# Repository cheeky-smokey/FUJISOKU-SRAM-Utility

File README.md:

# FUJISOKU SRAM Utility

> **このブランチ（`wo62256`）は v3.0 です。まだ実機では確かめていません。**
> 62256 をやめ、カードの F32〜F35（A16〜A19）を MCP23S17 ch7（U2）の GPB4〜GPB7 につなぐ設計にしました。カードは PC から 1MB まで読み書きできます。v2.8 の基板とは ch7 ポート B の配線が違います（[v2.8 からの変更](#v28-からの変更ハードウェア)）。
> 動作確認済みのリリース版 v2.8 は main ブランチと [Releases](https://github.com/cheeky-smokey/FUJISOKU-SRAM-Utility/releases) にあります。

Silver Reed 編み機のメモリカード（FUJISOKU SRAM、基本は 32KB。PC からは 1MB まで）を、Arduino UNO R4 で読み書きするツールです。MCP23S17 を 2 個使った GPIO エキスパンダでカードのアドレス・データ・制御線を直接動かし、PC・SD カード・SPI SRAM との間でコピーと照合をします。

- **PC から操作**: ブラウザの Web アプリで、カードを PC に保存・PC のファイルをカードに書き込み・比較。読み込みも書き込みも 32KB〜1MB の大きさをボタンで選べます。
- **表示**: 状態・処理の段階・進捗バー・結果を 20 文字 × 4 行で表示。同じ画面が Web アプリにも出るので、LCD はオプションです。
- **SD カード（オプション）**: 本体だけでカード ⇄ SD のバックアップ・照合・書き戻し。SD カードは処理の合間に抜き差しでき、最初から入っていなくても止まりません。
- **カードの検出と電池電圧**: カードが入っていなければ操作を止め、カードの電池電圧を LCD と Web アプリに表示します。1.70 V 以下で「少ない」（Low battery）、0.50 V 以下で「電池なし」と警告します。
- **シールド基板とスロットユニット**: Arduino UNO R4 に重ねるシールド基板（KiCad、ガーバー付き）に、U-BOX から外したスロットで作るスロットユニットを直接挿します。

## 使い方

1. 本体にこのブランチのスケッチ（v3.0）を書き込み、USB で PC につなぐ。
2. PC の **Google Chrome** または **Microsoft Edge** で [`webapp/FSRAM-Utility.html`](webapp/FSRAM-Utility.html) を開き、「本体に接続」を押してシリアルポートを選ぶ。
3. 目的のタブを選ぶ。

| タブ | できること |
|---|---|
| PC に保存 | カードを読み込んで `.bin` に保存。読み込む大きさは 32KB（既定）/ 64KB / 128KB / 256KB / 512KB / 1MB のボタンで選ぶ。2 回読んで一致を確かめる設定あり |
| カードに書き込み | `.bin`（32KB〜1MB）をカードへ。書き込む大きさは 32KB / 64KB / 128KB / 256KB / 512KB / 1MB のボタンで選ぶ（既定はファイルの大きさ）。32KB より大きく書くときは「先頭 32KB だけ」か「すべて」かを警告で選ぶ。書き込む前の自動保存、変わった部分だけの書き込み、書き込み後の照合 |
| 比較 | カードとファイル、またはファイル同士を比較。違いはメモリマップと 16 進表示に赤で出る |
| SD カード | 本体の SD カードとの保存・照合・書き込み、ファイル一覧（SD を使う設定のときだけ表示） |
| SPI SRAM・診断 | SPI SRAM とのコピー・比較・消去、SPI SRAM の自己診断（SPI SRAM を使う設定のとき）、カードの消去 |

「カードに書き込み」「比較」のファイル欄は、クリックかドロップで選び直せ、右の × で外せます。ふつうのカードは 32KB です。容量の大きいカードのときだけ大きさを変えてください（32KB のカードに 32KB を超えて書くと、先頭が上書きされます）。

Web アプリの詳しい説明は [docs/webapp.md](docs/webapp.md)、シリアルコマンドは [docs/protocol.md](docs/protocol.md) にあります。従来の 1 文字コマンド（`B` `L` `V` `R` `C` `X` `S` `W` `T` `E` `e`）もそのまま使えます。

## ハードウェア

### 必要なもの

| 区分 | 部品 | `config.h` |
|---|---|---|
| 必須 | Arduino UNO R4（Minima / WiFi） | - |
| 必須 | [シールド基板](#シールド基板) rev 2.0（MCP23S17 × 2 などを載せる。ユニバーサル基板で同じ結線にしてもよい） | - |
| 必須 | [スロットユニット](#スロットユニット)（U-BOX から外したスロット + 変換基板 + L 型のキー付きボックスヘッダ） | - |
| オプション | 20 × 4 キャラクタ LCD（HD44780 + PCF8574 の I2C バックパック。5V・GND・SDA = A4・SCL = A5） | `USE_LCD`（既定 1） |
| オプション | SD カードモジュール（5 V で使えるもの。/CS は D7） | `USE_SD`（既定 0） |
| オプション | SPI SRAM（23LC512。本体だけでのコピー・比較の一時置き場。/CS は D6） | `USE_SPI_SRAM`（既定 1。起動時に自動検出） |
| 配線 | カードの検出（カードの F37 /CARD DET → D2。シールド基板は配線済み） | `USE_CARD_DET`（既定 1） |
| 配線 | 電池電圧（カードの F2 BATT-DET → A2。A2 と GND の間に 1 MΩ。シールド基板は配線済み） | `USE_BATT_DET`（既定 1） |

カードの吸い出し・書き込み・比較は Web アプリでできるので、必須なのは Arduino UNO R4、シールド基板（MCP23S17 × 2）、スロットユニットだけです。電源は 5 V で、部品はすべて 5 V 系なのでレベル変換は要りません。

### シールド基板

| 項目 | 内容 |
|---|---|
| 大きさ | 68.58 × 53.34 mm（Arduino UNO と同じ形。右側の角が斜め） |
| 層・厚さ | 2 層、1.6 mm |
| 部品 | すべてスルーホール、IC は DIP（MCP23S17 × 2、23LC512、カードの電源のコンデンサ、BATT-DET のプルダウン、SD・LCD 用のピンヘッダ） |
| 取り付け穴 | φ3.2 mm × 4（UNO と同じ位置） |
| カードの接続 | J1 = キー付き MIL メスソケット 40P（キーは奥 = U1 側）。スロットユニットを直接挿す |
| データ | [hardware/kicad/shield/](hardware/kicad/shield/)（`.kicad_pcb`、ガーバー zip、原寸 PDF） |

部品表・注文のしかた（JLCPCB などの設定）・組み立ての注意は [hardware/kicad/README.md](hardware/kicad/README.md#シールド基板arduino-uno-r4-用) にあります。

### スロットユニット

FUJISOKU のカードスロットは製造中止なので、U-BOX から外したスロットを使います。スロットの足（ZIP 配列）を、秋月電子の 2.54 mm（2×5）⇔ 1.27 mm（1×10）変換基板 4 枚（表裏を逆にして使う）で 2 列にし、L 型のキー付きボックスヘッダ（2×20）を付けます。

- **シールドにつなぐ**: シールドの J1 に直接挿します。ボックスヘッダの切り欠きにソケットのキーが入るので、逆向きには挿さりません。
- **U-BOX につなぐ**: U-BOX の CN2 に足を ZIP 配列に曲げたボックスヘッダを付け、ストレートの 40 芯リボンケーブルでつなぎます。
- **ヘッダのピン**: 1 番 = F2、2 番 = F1（下段）、3 番 = F4、4 番 = F3 … 37 番 = F38、38 番 = F37。39・40 番は空き（奇数ピン 2k−1 = F2k、偶数ピン 2k = F2k−1）。

作り方と参考写真は [docs/hardware.md §12](docs/hardware.md#12-スロット記事より) にあります。

### カードの信号の割り当て（v3.0）

| 信号 | カードのピン | つなぐ先 |
|---|---|---|
| A0〜A15 | F16〜F31 | ch6（U1）の GPA0〜GPA7・GPB0〜GPB7 |
| D0〜D7 | F8〜F15 | ch7（U2）の GPA0〜GPA7 |
| CE2 / /OE / /CE1 / /WE | F5 / F7 / F4 / F6 | ch7（U2）の GPB0 / GPB1 / GPB2 / GPB3 |
| A16〜A19 | F32〜F35 | ch7（U2）の GPB4〜GPB7 |
| BATT-DET / /CARD DET | F2 / F37 | Arduino の A2 / D2 |
| Vcc / GND | F3・F36 / F1・F38 | 5 V / GND |

詳しい結線表・ピン配置・アクセス手順は [docs/hardware.md](docs/hardware.md) にあります。KiCad の回路図（PDF 付き）は [hardware/kicad/](hardware/kicad/) にあります。

### v2.8 からの変更（ハードウェア）

| 項目 | v2.8（main） | v3.0（このブランチ） |
|---|---|---|
| ch7 GPB0〜GPB3 | CE2（62256 の /CS と共用）、/OE、62256 の /OE、/WE | CE2、/OE、**/CE1**、/WE |
| ch7 GPB4〜GPB7 | /CE1、未使用、A16、A17 | **A16、A17、A18、A19** |
| カードの F34・F35（A18・A19） | GND に固定 | **U2 の GPB6・GPB7** |
| カードの範囲（PC から） | 256KB（A0〜A17） | **1MB（A0〜A19）** |
| 62256 | オプション（`USE_SRAM62256`） | **使わない** |
| シールド基板 | rev 1.x | **rev 2.0**（U2 の GPB の配線が違う。ガーバーも別） |

v2.8 の基板を v3.0 で使うときは、ch7 の GPB2 と GPB4〜GPB7 の配線を上の表のとおりにやり直してください。

## 設定（`config.h`）

オプション部品は `FUJISOKU_SRAM_COPY/config.h` の先頭で選びます。既定は SD カードなし、LCD と SPI SRAM はあり（どちらも見つからなければ飛ばして動く）です。

```c
#define USE_SD 0          // SD カードをつないだら 1 (SdFat ライブラリが要る)
#define USE_LCD 1         // LCD をつながないなら 0 (LiquidCrystal I2C ライブラリも不要になる)
#define USE_SPI_SRAM 1    // SPI SRAM をつながないなら 0 (1 のままでも、見つからなければ飛ばす)
#define USE_CARD_DET 1    // D2 にカードの検出を配線していないなら 0
#define USE_BATT_DET 1    // A2 にカードの電池電圧を配線していないなら 0
#define BATT_NONE_MV 500  // これ以下は「電池なし」(No battery) [mV]
#define BATT_LOW_MV 1700  // これ以下は「少ない」(Low battery) [mV]。BATT_NONE_MV より大きくする
```

`USE_LCD` と `USE_SPI_SRAM` は 1 のままでも、起動時に見つからなければその部品を使わずに動きます（SPI SRAM を使う操作は `ERR NOSPI` になり、Web アプリは自己診断だけを出します）。LCD の I2C アドレスは `LCD_I2C_ADDR`（既定 `0x27`、表示されないときは `0x3F`）です。

## ビルド

1. Arduino IDE のライブラリマネージャで、使う部品に合わせて入れる（SD と LCD を使わないなら不要）。
   - **SdFat**（Bill Greiman、v2 系）。`USE_SD` を 1 にしたときだけ必要です（既定の 0 なら不要）。
   - **LiquidCrystal I2C**（Frank de Brabander）。`USE_LCD` が 1 のときだけ必要です。「AVR 用」と警告が出ることがありますが、UNO R4 でも使えます。
2. `FUJISOKU_SRAM_COPY/FUJISOKU_SRAM_COPY.ino` を開いてボードに書き込む（同じフォルダの `.ino` と `config.h` はタブとして一緒に開かれます）。

## 構成

```
FUJISOKU_SRAM_COPY/         スケッチ (メイン、config.h、hardware / storage / operations / protocol / lcd_ui / card)
webapp/FSRAM-Utility.html   Web アプリ (1 ファイル、インストール不要)
docs/                       hardware.md (配線)、specification.md (ソフト仕様)、protocol.md (通信)、webapp.md
hardware/kicad/             KiCad の回路図 (.kicad_sch、PDF)、作り直し・確認用のスクリプト
hardware/kicad/shield/      UNO R4 用シールド基板 rev 2.0 (.kicad_pcb、ガーバー zip、原寸 PDF)
test/                       PC 上でスケッチを動かすシミュレータと自動テスト (test/README.md)
```

## 確かめたこと

スケッチをそのまま PC でビルドし、MCP23S17・カード・SPI SRAM・SD カード・LCD を再現したシミュレータで動かして、66 件の自動テスト（ファームウェア 30、表示 9、Web アプリ 27。SD・LCD・SPI SRAM・カード検出のあり・なしの構成と、1MB のカードの読み書きを含む）が通ることを確認しています。本物の SdFat と LiquidCrystal I2C のヘッダに対する型チェックも通っています。シールド基板は DRC（エラー 0、未配線 0）と、銅のつながりを [docs/hardware.md](docs/hardware.md) の結線表と照らし合わせて確かめています。変更点は [docs/specification.md §12](docs/specification.md#12-変更履歴)、テストは [test/README.md](test/README.md) にあります。

**実機（Arduino UNO R4 と作者の基板）での動作は v2.8 まで確認済みです。v3.0 の新しい割り当てとシールド基板 rev 2.0 は、まだ実機で確かめていません。**

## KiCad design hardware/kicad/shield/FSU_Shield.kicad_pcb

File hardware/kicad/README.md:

# 回路図・シールド基板（KiCad）

FUJISOKU SRAM Utility の回路図と、Arduino UNO R4 用のシールド基板です。[docs/hardware.md](../../docs/hardware.md) の結線表と `FUJISOKU_SRAM_COPY/config.h` のピン定義（v3.0、ブランチ `wo62256`）から作りました。シールド基板は rev 2.0 で、main（v2.8）の rev 1.x とは U2 GPB の配線が違います。**v3.0 の割り当ては、まだ実機では確かめていません。**

- [回路図](#回路図)（スロットも含む全体）
- [シールド基板](#シールド基板arduino-uno-r4-用)（ガーバー付き。カードのスロットユニットを J1 に直接挿す）
- [スロットユニット](#スロットユニット)（U-BOX から外したスロット + 変換基板 + L 型ボックスヘッダ）

## 回路図

| ファイル | 内容 |
|---|---|
| `FUJISOKU_SRAM_Utility.kicad_pro` / `.kicad_sch` | KiCad のプロジェクトと回路図（KiCad 7 で作成。8 / 9 でも開ける） |
| `FUJISOKU_SRAM_Utility.pdf` | 印刷・閲覧用の PDF（A3） |
| `gen_schematic.py` | 回路図を作るスクリプト。結線を変えるときはここを直して作り直す（`--shield` でシールド基板用の回路図） |
| `check_netlist.py` | 回路図の結線が仕様書どおりかを確かめるスクリプト（`--shield` でシールド基板用） |

### 載っている部品

| 部品番号 | 部品 | 備考 |
|---|---|---|
| A1 | Arduino UNO R4 | KiCad の UNO R3 の形（ピン配置は同じ） |
| U1 | MCP23S17 ch6 | アドレス A0〜A15。A2:A0 = 110 |
| U2 | MCP23S17 ch7 | データ D0〜D7、制御線（GPB0〜GPB3）、A16〜A19（GPB4〜GPB7）。A2:A0 = 111 |
| J1 | FUJISOKU カードのスロット（F1〜F38） | ピン番号 n = カードのピン Fn。F32〜F35 = A16〜A19（U2 GPB4〜GPB7） |
| R1 | 1 MΩ | BATT-DET（A2）のプルダウン |
| U3 | 23LC512（オプション） | SPI SRAM、/CS = D6 |
| J2 | SD カードモジュール（オプション） | 5 V 用。/CS = D7。ピンの並びはモジュールによって違う |
| J3 | 20×4 LCD + PCF8574（オプション） | I2C、アドレス 0x27 |
| C1〜C3 / C4 | 0.1 µF / 10 µF | 各 IC の近くのパスコンと電源の電解コンデンサ（推奨。仕様書には無い部品） |

- 部品どうしは、ピンに付けた名前（ネットラベル）でつないでいます。同じ名前のラベルがつながっています。
- 電源は Arduino の 5V ピンから取る 5 V だけです。部品はすべて 5 V 系で、レベル変換はありません。

## シールド基板（Arduino UNO R4 用）

| 表 | 裏（裏から見た向き） |
|---|---|
|  |  |

- 大きさは Arduino UNO と同じ（68.58 × 53.34 mm、右側の角が斜め）。2 層、厚さ 1.6 mm。取り付け穴は φ3.2 mm × 4（UNO と同じ位置）。UNO R4 Minima / WiFi に重ねて使います。
- 部品はすべてスルーホールで、IC は DIP（ソケット）です。
- カードは、[スロットユニット](#スロットユニット)を **J1（キー付きの MIL メスソケット）に直接挿して**つなぎます。ユニットのボックスヘッダの切り欠きにソケットのキーが入るので、逆向きには挿さりません。キーは奥（U1 側、シルクの KEY）です。
  J1 のピンとカードのピンの対応は、スロットユニットのヘッダと同じです。

  | J1 のピン | 1 | 2 | 3 | 4 | 5 | 6 | … | 37 | 38 | 39 | 40 |
  |---|---|---|---|---|---|---|---|---|---|---|---|
  | カード | F2 | F1 | F4 | F3 | F6 | F5 | … | F38 | F37 | 空き | 空き |

  （2k−1 番 = F2k、2k 番 = F2k−1）。F32〜F35（A16〜A19）は U2 の GPB4〜GPB7 につないでいます。
- 配線は自動配線（Freerouting）で、表と裏に GND のベタを敷いています。ビアは 13 個です。
- 確認済み: DRC（設計ルールの確認）でエラーと未配線は 0、基板の銅のつながりを `check_netlist.py --shield` で仕様書の結線表と照合。

### ファイル（`shield/`）

| ファイル | 内容 |
|---|---|
| `gerber/FSU_Shield_gerber.zip` | **基板メーカーに出すデータ**（ガーバーとドリル） |
| `FSU_Shield.kicad_pro` / `.kicad_pcb` / `.kicad_sch` | KiCad のプロジェクト、基板、回路図 |
| `FSU.pretty/`、`fp-lib-table` | シールド用の Arduino のフットプリント（下の注意を参照）と、J1 のキー付きメスソケットのフットプリント |
| `FSU_Shield_top.png` / `_bottom.png` | 基板の見た目（確認用） |
| `FSU_Shield_1to1.pdf` | 原寸の図（A4 に 100 % で印刷して Arduino を重ね、ピンの位置を確かめる用） |
| `drc_report.txt` | DRC の結果 |
| `../gen_pcb.py` | 基板を作るスクリプト（配置、自動配線、ベタ、DRC、ガーバー） |

### 部品表

| 部品番号 | 部品 | 個数 | 備考 |
|---|---|---|---|
| U1, U2 | MCP23S17-E/SP（DIP-28、幅 7.62 mm） | 2 | 28 ピン IC ソケット（300 mil）を使う |
| U3 | 23LC512-I/P（DIP-8） | 1 | オプション。8 ピン IC ソケット。挿さなくても動く（自動検出） |
| J1 | MIL コネクタのメスソケット 40P（2×20、2.54 mm、基板用ストレート、キー付き） | 1 | ボックスヘッダに挿さるもの。キーを奥（U1 側、シルクの KEY）に向ける |
| J2 | ピンヘッダ 1×6 | 1 | SD カードモジュール（オプション）。ジャンパ線でつなぐ |
| J3 | ピンヘッダ 1×4 | 1 | LCD（オプション）。GND、5V、SDA、SCL |
| R1 | 1 MΩ 1/4 W | 1 | BATT-DET（A2）のプルダウン |
| C1〜C3 | 0.1 µF 積層セラミック、足の間隔 5 mm（5.08 mm の部品も入る） | 3 | U1〜U3 のパスコン。VDD・VSS のピンのすぐ横 |
| C4 | 10 µF 電解（16 V 以上、直径 5 mm、足の間隔 2.5 mm。2 mm の部品は足を少し広げて挿す） | 1 | カードの電源用。+ の向きに注意 |
| — | ピンヘッダ（オス）1×10、1×8、1×8、1×6 | 各 1 | Arduino に挿す側。普通のシールドと同じく裏から差して表ではんだ付け |

### 注文のしかた

1. `shield/gerber/FSU_Shield_gerber.zip` を、そのまま JLCPCB、PCBWay、Elecrow などにアップロードします。
2. 設定は標準のままで作れます: 2 層、1.6 mm、線幅 0.3 mm 以上（電源 0.6 mm）、間隔 0.25 mm 以上、ビア 0.8 mm（穴 0.4 mm）。層数と大きさはガーバーから自動で読み取られます。JLCPCB の場合の例:

   | 項目 | 設定 |
   |---|---|
   | Base Material / Layers | FR-4 / 2 |
   | PCB Qty | 5（最少） |
   | Delivery Format | Single PCB |
   | PCB Thickness | 1.6 mm |
   | PCB Color / Silkscreen | Green / White（ほかの色は高くなったり日数が延びたりすることがある） |
   | Surface Finish | HASL（有鉛または鉛フリー。スルーホールだけなので ENIG は要らない） |
   | Outer Copper Weight | 1 oz |
   | Mark on PCB（注文番号） | Remove Order Number（1〜6 層は手数料なし） |
   | そのほか | 既定のまま |
3. 注文の前に、`FSU_Shield_1to1.pdf` を A4 に **100 %（拡大縮小なし）** で印刷し、Arduino を重ねてピンの位置を確かめると確実です。

### 組み立て・使うときの注意

- **IC の向きに注意**: U1・U2 は U3 と逆向きです（U1・U2 は切り欠きが右、1 番ピンが右上。U3 は切り欠きが左、1 番ピンが左下）。シルクの切り欠きと四角いパッド（1 番ピン）に合わせて挿します。
- **J1 はキー（シルクの KEY と四角い出っ張り）を奥（U1 側）に向けて**付けます。1 番ピン（▽ の印、四角いパッド）は右端です。
- スロットユニットは、変換基板が手前（電源ヘッダ側）、カードのラベル面が奥を向く向きで挿さります。ボックスヘッダの口はシールドから約 2 mm 上に来るので、J1 の周りには背の高い部品を置いていません。
- **DC ジャック（左下）と ICSP ヘッダ（右の中ほど）の上には、部品の足が出ないように**配置してあります。USB-C の上（左上）には U3 があります（UNO R4 の USB-C は背が低いので当たりません）。
- 部品面の左下（取り付け穴の上、C4 の左）のシルクに「Powered by」「Cheeky-Smokey」の 2 行で入れています。
- MCP23S17 のアドレス（A2:A0）は基板の配線で決めてあります（U1 = 110、U2 = 111）。設定は要りません。
- J2（SD）は、モジュールによってピンの並びが違うので、シルクの名前（GND、5V、MISO、MOSI、SCK、CS）を見てジャンパ線でつなぎます。5 V で使えるモジュールを使います。
- U2 の GPB は B0 = CE2、B1 = /OE、B2 = /CE1、B3 = /WE、B4〜B7 = A16〜A19 です（v2.8 では /CE1 が B4、F34・F35 が GND）。

### スロットユニット

FUJISOKU のカードスロットは製造中止で手に入らないため、U-BOX から外したスロットを使い、シールドにも U-BOX にもつなげるユニットにします。

| 部品 | 個数 | 備考 |
|---|---|---|
| FUJISOKU カードスロット（U-BOX から外したもの） | 1 | 足は ZIP 配列。1 列にそろえて変換基板の 1.27 mm の穴に挿す |
| 秋月電子 2.54 mm（2×5）⇔ 1.27 mm（1×10）変換基板 | 4 | **表裏を通常と逆にして**使う。40 か所のうち 38 か所を使う |
| L 型（ライトアングル）ボックスヘッダ 2×20、2.54 mm、キー付き | 1 | 変換基板の 2×5 の穴に付ける |

- ヘッダの 1 番 = F2（上段）、2 番 = F1（下段 = 変換基板に近い列）… 37 番 = F38、38 番 = F37。39・40 番は空き。変換基板を表裏逆にするのは、奇数の F を下段にするためです。
- **シールドにつなぐ**: J1 に直接挿します（上の注意を参照）。
- **U-BOX につなぐ**: U-BOX の CN2 に、足を ZIP 配列に曲げたボックスヘッダを付け、ストレートの 40 芯リボンケーブル（両端 IDC ソケット）でつなぎます。CN2 の 1 番（F1）はボックスヘッダの 2 番に来るので、スロットユニットも 2 番 = F1 にしています。
- 切り欠き（キー）の位置は製品によって違うことがあります。買ったボックスヘッダとソケットで、正しい向きのときだけ挿さることを確かめてください。

### KiCad の標準の Arduino のフットプリントについて

KiCad 標準の `Module:Arduino_UNO_R3` は、上から見るとデジタル側のヘッダが下に来る向き（Arduino を裏返して載せる向き）で描かれています。シールドにそのまま使うと鏡に映した形になり、Arduino に挿せません。この基板では、それを上下反転した `FSU:Arduino_UNO_R4_Shield`（`shield/FSU.pretty`、原点は Arduino の基板の左下）を使っています。パッド番号は標準と同じなので、シンボル `MCU_Module:Arduino_UNO_R3` とそのまま対応します。

## 作り直す・確かめる

KiCad 7 以降が入った PC で次を実行します。

```sh
python3 gen_schematic.py                       # 回路図を作り直す (KiCad の標準シンボルライブラリを使う)
kicad-cli sch export pdf -o FUJISOKU_SRAM_Utility.pdf FUJISOKU_SRAM_Utility.kicad_sch
kicad-cli sch export netlist --format kicadsexpr -o /tmp/fsu.net FUJISOKU_SRAM_Utility.kicad_sch
python3 check_netlist.py /tmp/fsu.net          # 結線を確かめる (OK と出れば仕様書どおり)
```

`check_netlist.py` は、カードのピン・MCP23S17・Arduino・SPI の各部品のつながり（カードの F32〜F35 → U2 GPB4〜GPB7 を含む）と、+5V・GND、未接続のピン（MCP の INT など）を、仕様書の表と照らし合わせます。

シールド基板は次のとおりです。`gen_pcb.py` には KiCad の標準フットプリント（`kicad-footprints`）、Java と [Freerouting](https://github.com/freerouting/freerouting) 1.9 が要ります（`FREEROUTING_JAR` で jar の場所を指定。画面の無い環境では `xvfb-run` を使う）。

```sh
python3 gen_schematic.py --shield              # shield/FSU_Shield.kicad_sch
python3 gen_pcb.py                             # 基板、DRC、仕様書との照合、ガーバー、画像
python3 gen_pcb.py --retext                    # 配線はそのままで、シルクの文字だけ書き直して出力し直す
```

自動配線は実行のたびに少し違う結果になります（全部つながるまで自動でやり直します）。

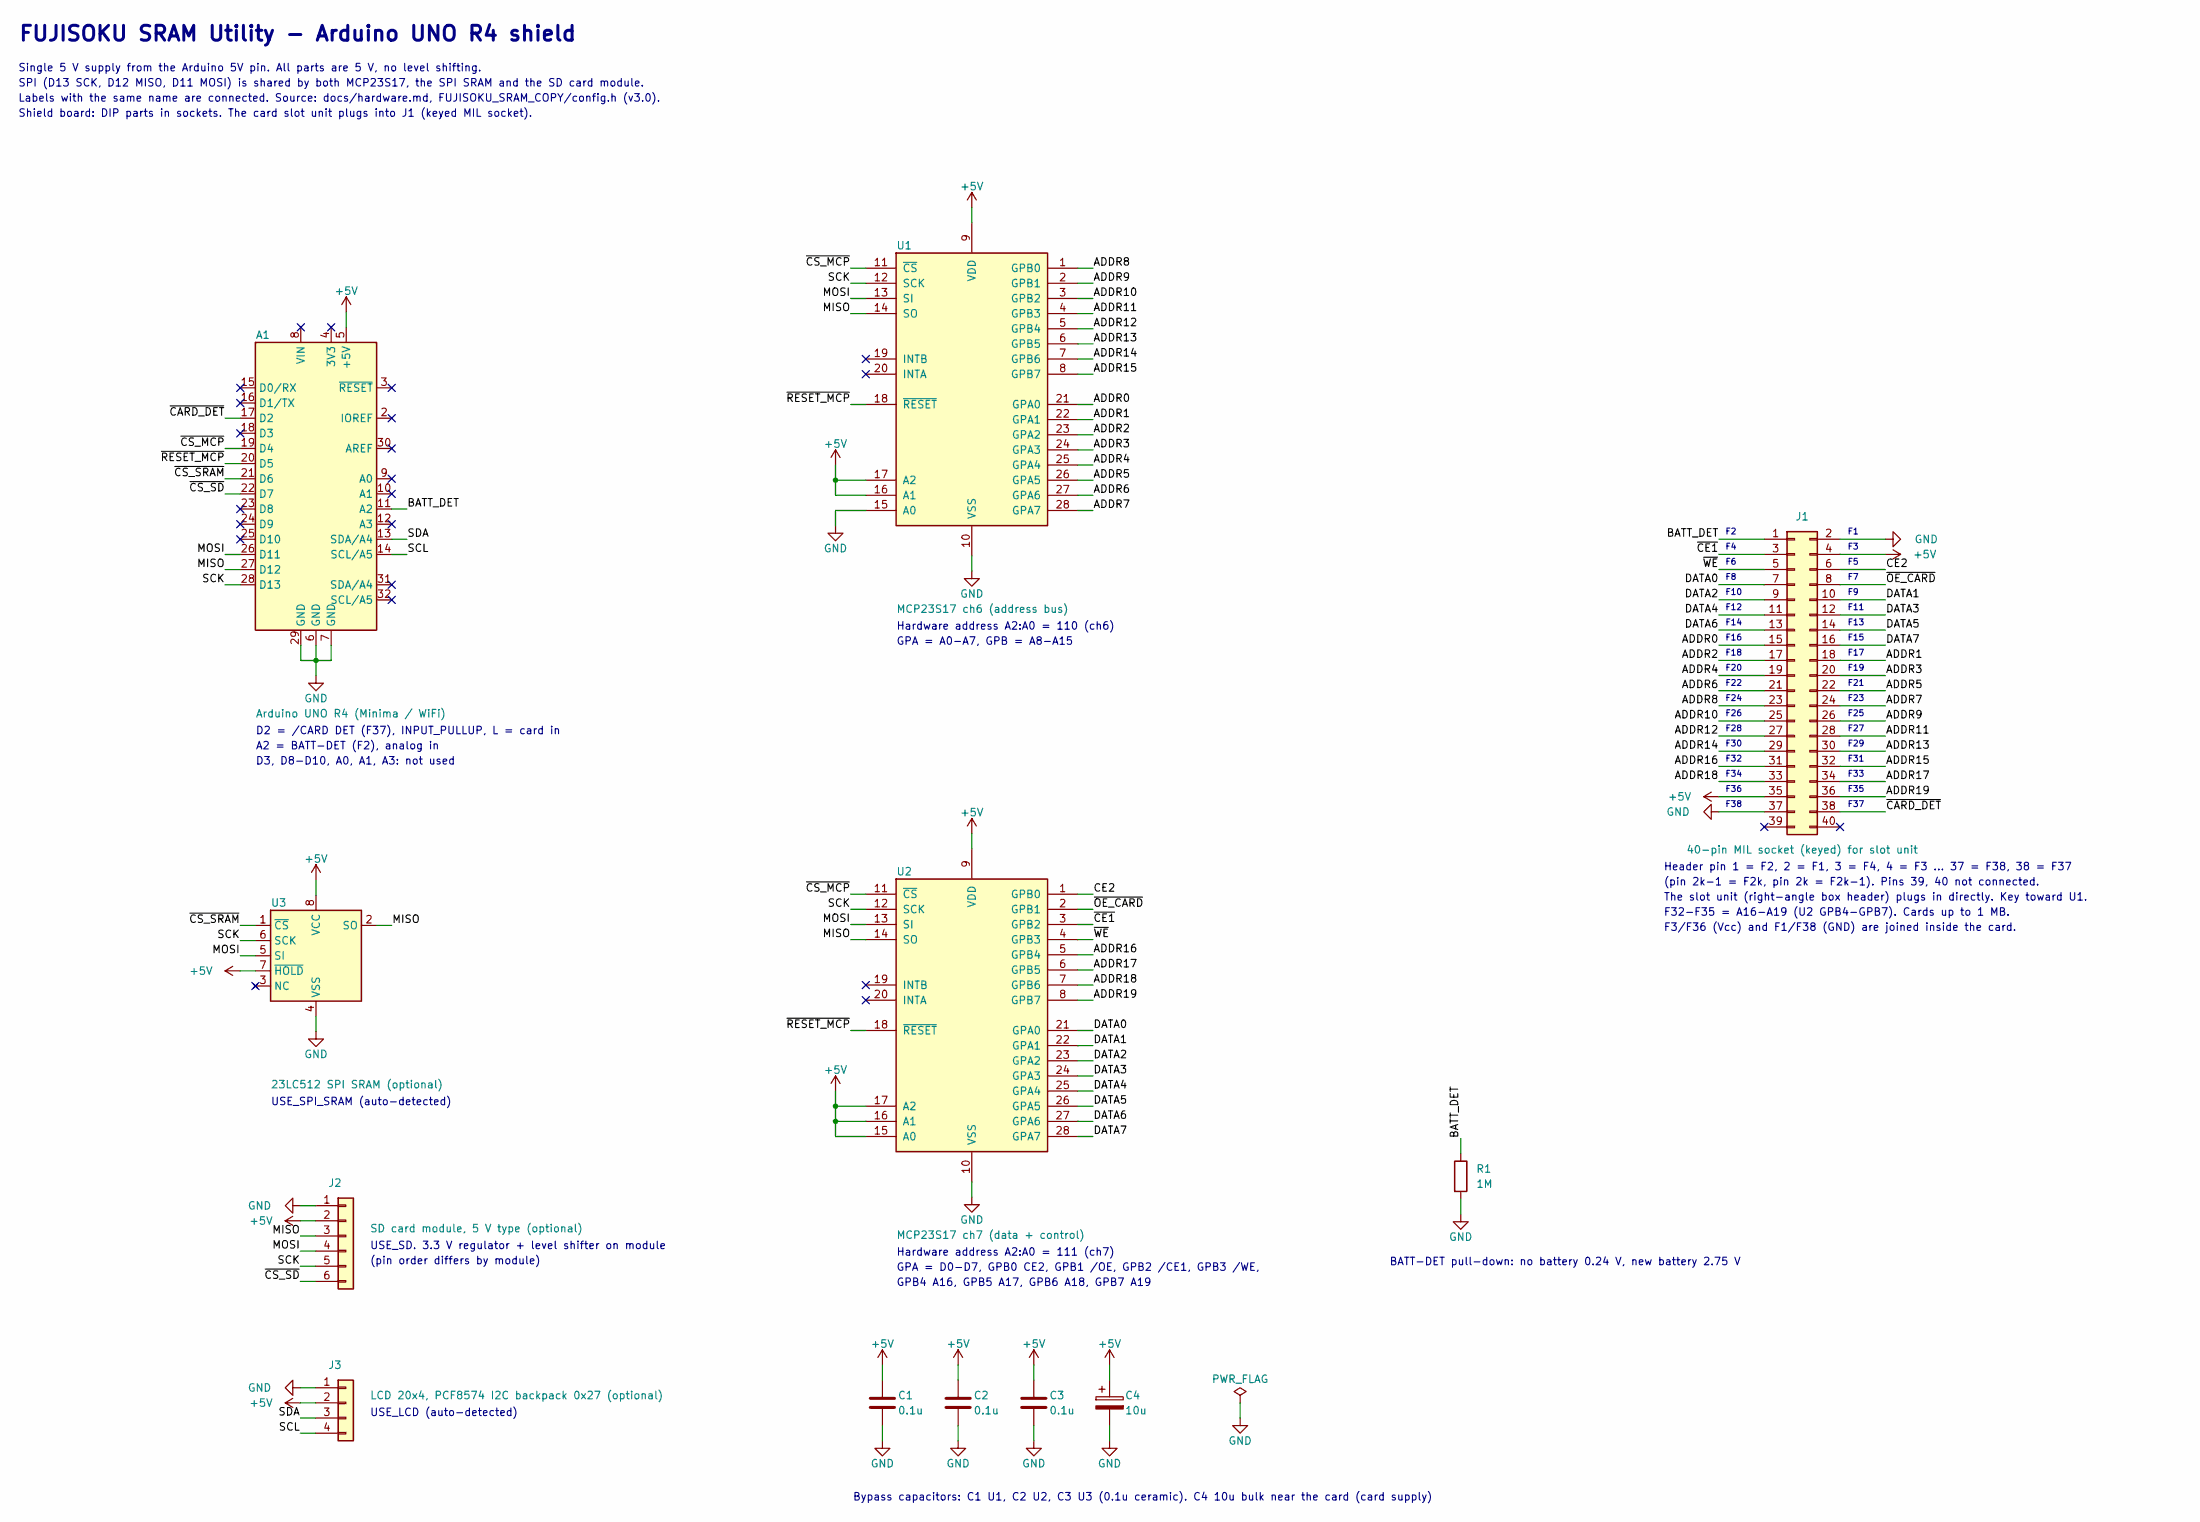
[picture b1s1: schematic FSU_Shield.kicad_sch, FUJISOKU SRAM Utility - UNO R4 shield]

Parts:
A1: Arduino UNO R4 (Minima / WiFi); Arduino_UNO_R4_Shield
C1, C2, C3: 0.1u; C_Disc_D5.0mm_W2.5mm_P5.00mm
C4: 10u; CP_Radial_D5.0mm_P2.50mm
J1: 40-pin MIL socket (keyed) for slot unit; MIL_Socket_2x20_P2.54mm_Vertical
J2: SD card module, 5 V type (optional); PinHeader_1x06_P2.54mm_Vertical
J3: LCD 20x4, PCF8574 I2C backpack 0x27 (optional); PinHeader_1x04_P2.54mm_Vertical
R1: 1M; R_Axial_DIN0207_L6.3mm_D2.5mm_P7.62mm_Horizontal
U1: MCP23S17 ch6 (address bus); DIP-28_W7.62mm_Socket
U2: MCP23S17 ch7 (data + control); DIP-28_W7.62mm_Socket
U3: 23LC512 SPI SRAM (optional); DIP-8_W7.62mm_Socket

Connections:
+5V: A1.5 (+5V), C1.1, C2.1, C3.1, C4.1, J1.4, J1.35, J2.2, J3.2, U1.9 (VDD), U1.16 (A1), U1.17 (A2), U2.9 (VDD), U2.15 (A0), U2.16 (A1), U2.17 (A2), U3.7 (~HOLD), U3.8 (VCC)
/ADDR0: J1.15, U1.21 (GPA0)
/ADDR1: J1.18, U1.22 (GPA1)
/ADDR2: J1.17, U1.23 (GPA2)
/ADDR3: J1.20, U1.24 (GPA3)
/ADDR4: J1.19, U1.25 (GPA4)
/ADDR5: J1.22, U1.26 (GPA5)
/ADDR6: J1.21, U1.27 (GPA6)
/ADDR7: J1.24, U1.28 (GPA7)
/ADDR8: J1.23, U1.1 (GPB0)
/ADDR9: J1.26, U1.2 (GPB1)
/ADDR10: J1.25, U1.3 (GPB2)
/ADDR11: J1.28, U1.4 (GPB3)
/ADDR12: J1.27, U1.5 (GPB4)
/ADDR13: J1.30, U1.6 (GPB5)
/ADDR14: J1.29, U1.7 (GPB6)
/ADDR15: J1.32, U1.8 (GPB7)
/ADDR16: J1.31, U2.5 (GPB4)
/ADDR17: J1.34, U2.6 (GPB5)
/ADDR18: J1.33, U2.7 (GPB6)
/ADDR19: J1.36, U2.8 (GPB7)
/BATT_DET: A1.11 (A2), J1.1, R1.1
/CE2: J1.6, U2.1 (GPB0)
/DATA0: J1.7, U2.21 (GPA0)
/DATA1: J1.10, U2.22 (GPA1)
/DATA2: J1.9, U2.23 (GPA2)
/DATA3: J1.12, U2.24 (GPA3)
/DATA4: J1.11, U2.25 (GPA4)
/DATA5: J1.14, U2.26 (GPA5)
/DATA6: J1.13, U2.27 (GPA6)
/DATA7: J1.16, U2.28 (GPA7)
/MISO: A1.27 (D12), J2.3, U1.14 (SO), U2.14 (SO), U3.2 (SO)
/MOSI: A1.26 (D11), J2.4, U1.13 (SI), U2.13 (SI), U3.5 (SI)
/SCK: A1.28 (D13), J2.5, U1.12 (SCK), U2.12 (SCK), U3.6 (SCK)
/SCL: A1.14 (SCL/A5), J3.4
/SDA: A1.13 (SDA/A4), J3.3
/~CARD_DET: A1.17 (D2), J1.38
/~CE1: J1.3, U2.3 (GPB2)
/~CS_MCP: A1.19 (D4), U1.11 (~CS), U2.11 (~CS)
/~CS_SD: A1.22 (D7), J2.6
/~CS_SRAM: A1.21 (D6), U3.1 (~CS)
/~OE_CARD: J1.8, U2.2 (GPB1)
/~RESET_MCP: A1.20 (D5), U1.18 (~RESET), U2.18 (~RESET)
/~WE: J1.5, U2.4 (GPB3)
GND: A1.6 (GND), A1.7 (GND), A1.29 (GND), C1.2, C2.2, C3.2, C4.2, J1.2, J1.37, J2.1, J3.1, R1.2, U1.10 (VSS), U1.15 (A0), U2.10 (VSS), U3.4 (VSS)

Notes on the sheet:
D2 = /CARD DET (F37), INPUT_PULLUP, L = card in
A2 = BATT-DET (F2), analog in
D3, D8-D10, A0, A1, A3: not used
Hardware address A2:A0 = 110 (ch6)
GPA = A0-A7, GPB = A8-A15
Hardware address A2:A0 = 111 (ch7)
GPA = D0-D7, GPB0 CE2, GPB1 /OE, GPB2 /CE1, GPB3 /WE,
GPB4 A16, GPB5 A17, GPB6 A18, GPB7 A19
F10
F12
F11
F14
F13
F16
F15
F18
F17
F20
F19
F22
F21
F24
F23
F26
F25
F28
F27
F30
F29
F32
F31
F34
F33
F36
F35
F38
F37
Header pin 1 = F2, 2 = F1, 3 = F4, 4 = F3 ... 37 = F38, 38 = F37
(pin 2k-1 = F2k, pin 2k = F2k-1). Pins 39, 40 not connected.
The slot unit (right-angle box header) plugs in directly. Key toward U1.

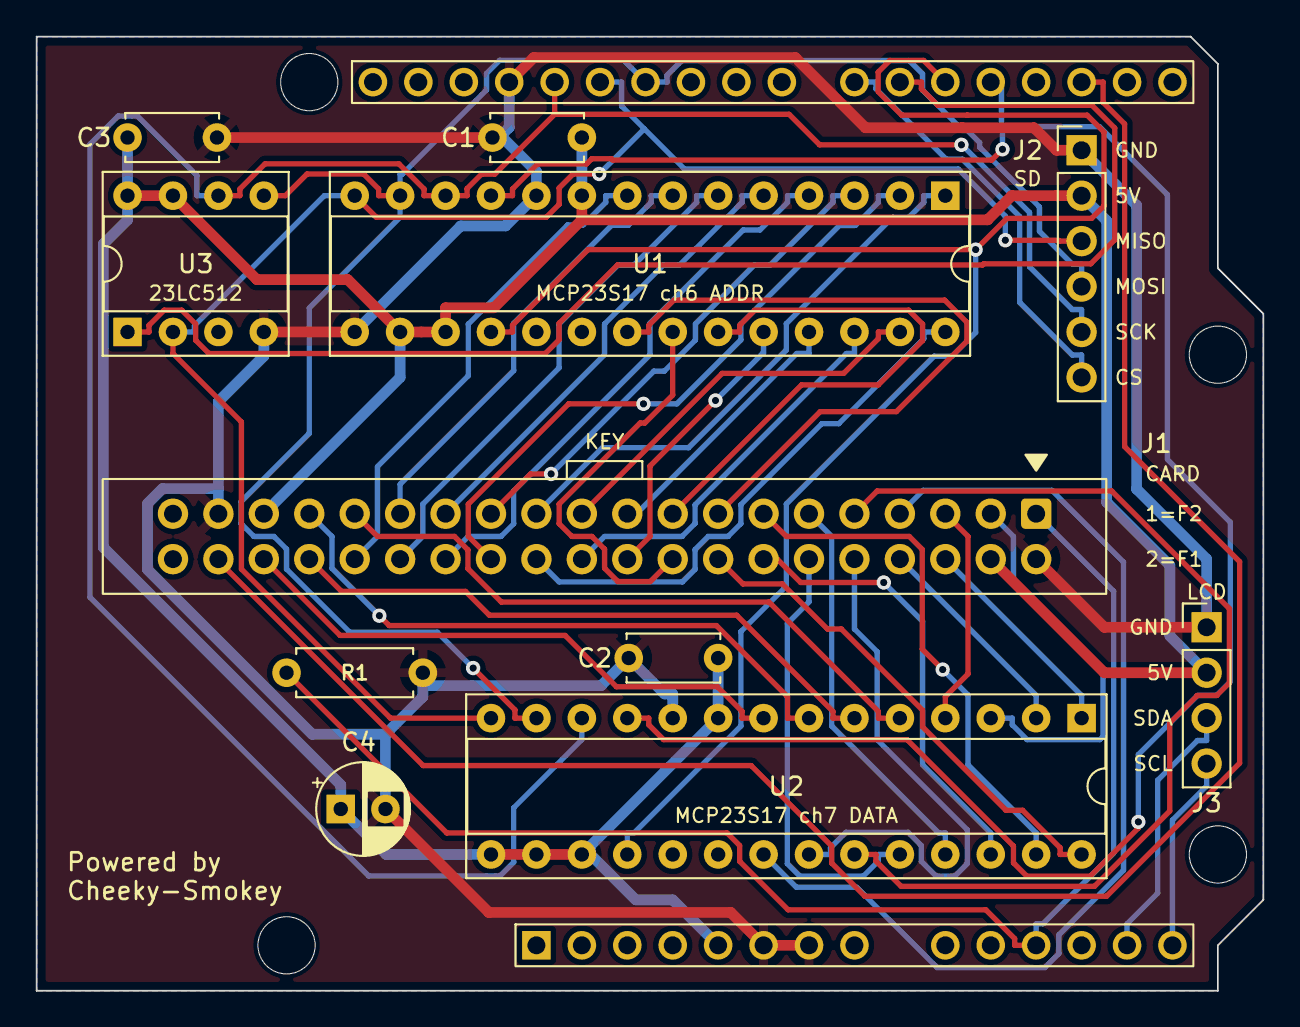
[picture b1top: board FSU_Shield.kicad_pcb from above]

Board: 2 copper layers, 68.6 x 53.3 mm, 12 parts (0 on the bottom side), 45 nets.

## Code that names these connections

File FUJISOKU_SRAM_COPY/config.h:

// FUJISOKU SRAM Utility - 設定・定数・共通定義
//
// つないだ部品に合わせて書き換えるのは、先頭の「オプション部品」だけ。
// それより下は配線と部品の仕様で決まる値 (docs/hardware.md と対応)。
#ifndef FSU_CONFIG_H
#define FSU_CONFIG_H

#include <Arduino.h>

#define FSU_VERSION "3.0"

// =====================================================================
// オプション部品 (1 = 使う、0 = 使わない)
//   必須: MCP23S17 x 2、FUJISOKU カードのスロット
//   カードの吸い出し・書き込み・比較は Web アプリ (PC) でできるので、ほかの部品はなくてもよい
// =====================================================================

// SD カード (本体だけでの保存・照合・書き戻し)。既定は 0 (カードの保存は Web アプリで PC にできる)。
//   1 にするには SdFat ライブラリが要る。起動時にカードが無くても、処理の合間に抜き差ししても動く。
//   0 のときは SdFat ライブラリは不要で、sd コマンドと B L V S W は ERR DISABLED を返す。
#ifndef USE_SD
#define USE_SD 0
#endif

// 20 文字 x 4 行のキャラクタ LCD (I2C)。
//   0 にすると LiquidCrystal I2C ライブラリも不要になる。
//   1 のままでも、起動時に LCD が見つからなければ表示を飛ばして動く (Web アプリには同じ内容が出る)。
#ifndef USE_LCD
#define USE_LCD 1
#endif

// SPI SRAM 23LC512 (本体だけでのコピー・比較の一時置き場、/CS = D6)。
//   1 のときは起動時に SPI SRAM があるかを確かめる。見つからなければ SPI SRAM を使う操作は ERR NOSPI を返す。
//   0 にすると SPI SRAM のコードが入らず、対象 s と R C X E S W T は ERR DISABLED を返す。
#ifndef USE_SPI_SRAM
#define USE_SPI_SRAM 1
#endif

// カードの検出 (カードの F37 /CARD DET → D2)。
//   1 にすると、カードが入っていないときはカードを使う操作が ERR NOCARD を返し、処理中に抜かれたら止める。
//   0 にすると、いつも入っているものとして扱う (D2 を配線していない基板)。
#ifndef USE_CARD_DET
#define USE_CARD_DET 1
#endif

// カードの電池電圧 (カードの F2 BATT-DET → A2)。A2 と GND の間に 1 MΩ の抵抗をつける
//   (つけないと、電池が無くてもカードの中の漏れ電流で 3〜4 V に見える)。
//   1 にすると、電圧を Web アプリと LCD に出し、BATT_NONE_MV 以下は「電池なし」、BATT_LOW_MV 以下は「少ない」と警告する。
#ifndef USE_BATT_DET
#define USE_BATT_DET 1
#endif

// 電池の判定電圧 [mV] (A2 で測った表示の値と比べる)。BATT_NONE_MV < BATT_LOW_MV にすること
//   電圧 <= BATT_NONE_MV                 → 「電池なし」(No battery)   既定 0.50 V
//   BATT_NONE_MV < 電圧 <= BATT_LOW_MV   → 「少ない」(Low battery)    既定 1.70 V
//   BATT_LOW_MV より上                   → 正常
//   作者の基板 (A2 に 1 MΩ) の実測: 電池なし 0.24 V、新品の電池 2.75 V
//   1.70 V は、テスターで測った電池の電圧で約 2 V (CR2016 は約 2.05 V、BR2325 は約 1.94 V。docs/hardware.md §6.1)
#ifndef BATT_NONE_MV
#define BATT_NONE_MV 500
#endif
#ifndef BATT_LOW_MV
#define BATT_LOW_MV 1700
#endif

// =====================================================================
// 設定
// =====================================================================

// LCD の I2C アドレス (PCF8574 バックパック)。作者の基板は 0x27。ほかのバックパックでは 0x3F のこともある
#ifndef LCD_I2C_ADDR
#define LCD_I2C_ADDR 0x27
#endif
#define LCD_COLS 20
#define LCD_ROWS 4

// 結果画面を表示しておく時間 [ms] (過ぎたら待機画面に戻る)
#ifndef RESULT_HOLD_MS
#define RESULT_HOLD_MS 15000
#endif

// MCP23S17 と SPI SRAM を操作するときの SPI クロック [Hz] (MCP23S17 の上限は 10 MHz)
#ifndef SPI_BUS_HZ
#define SPI_BUS_HZ 4000000
#endif

// /CARD DET の向き: 1 = カードが入ると Low (D2 は内蔵プルアップ)
#ifndef CARD_DET_ACTIVE_LOW
#define CARD_DET_ACTIVE_LOW 1
#endif

// A2 の測定範囲 [mV] (UNO R4 は 5V が基準)。テスターで測った 5V の値にすると電圧が正確になる
#ifndef BATT_ADC_FULL_MV
#define BATT_ADC_FULL_MV 5000
#endif

// SD カードの生存確認の間隔 [ms] (カードが READY のときだけ行う)
#ifndef SD_ALIVE_CHECK_MS
#define SD_ALIVE_CHECK_MS 1500
#endif

// =====================================================================
// データ量・識別子
// =====================================================================
#define CARD_SIZE 0x8000UL       // 本体だけの処理 (コピー・比較・消去・SD) が扱う範囲 0x0000-0x7FFF (32 KB)
#define CARD_MAX_SIZE 0x100000UL // PC からの rd / wr / fill でカードに使える範囲 (A0-A19 = 1 MB)
#define SPI_SRAM_SIZE 0x10000UL  // SPI SRAM 23LC512 (64 KB)
#define CHUNK_BYTES 64           // PC とのやりとりの 1 行あたりのバイト数
#define BLOCK_BYTES 256          // SD / コピー処理の 1 ブロック
#define ERASE_VALUE 0xFF         // 消去で書く値

// バックアップ中に使う一時ファイル名 (成功したら本来の名前に付け替える)
#define SD_TMP_NAME "FSU_TMP.TMP"

// 転送対象 (dev 引数)。コマンドでは f / s
#define DEV_SPI_SRAM 0   // s: SPI SRAM (USE_SPI_SRAM のときだけ)
#define DEV_FUJISOKU 1   // f: FUJISOKU カード

// SD カードの状態
#define SD_STATE_UNKNOWN 0
#define SD_STATE_ABSENT 1
#define SD_STATE_READY 2

// 処理結果
#define RES_OK 0
#define RES_NG 1
#define RES_ERR 2
#define RES_CANCEL 3

// =====================================================================
// Arduino のピン
//   SPI: D13 SCK / D12 MISO / D11 MOSI (MCP23S17、SPI SRAM、SD カードで共有)
//   I2C: A4 SDA / A5 SCL (LCD)
//   D0、D1、D3、D8、D9、D10、A0、A1、A3 は未使用
// =====================================================================
#define PIN_CS_SD 7        // SD カードの /CS。USE_SD = 0 でも High にしておく (モジュールが付いたままでも邪魔しない)
#define PIN_CS_SPI_SRAM 6  // SPI SRAM の /CS。USE_SPI_SRAM = 0 でも High にしておく
#define PIN_MCP_RESET 5    // MCP23S17 の /RESET (2 個共通)
#define PIN_CS_MCP 4       // MCP23S17 の /CS (2 個共通。ハードウェアアドレスで区別する)
#define PIN_MCP_INT 3      // 未接続 (MCP23S17 の INT は使わない。入力にしておくだけ)
#define PIN_CARD_DET 2     // カードの /CARD DET (F37)。内蔵プルアップの入力
#define PIN_BATT_DET A2    // カードの BATT-DET (F2)。アナログ入力

// =====================================================================
// MCP23S17 (GPIO エキスパンダ)
// =====================================================================
// チャネル = ハードウェアアドレス (A2 A1 A0 ピンの値)
#define MCP_CH_ADDR 6  // ch6: GPA = A0-A7、GPB = A8-A15
#define MCP_CH_DATA 7  // ch7: GPA = D0-D7
#define MCP_CH_CTRL 7  // ch7: GPB = 制御線 (下の CTRL_*)

// SPI のオペコード: 0 1 0 0 A2 A1 A0 R/W
#define MCP_OP_WRITE(ch) (0x40 | ((ch) << 1))
#define MCP_OP_READ(ch) (0x41 | ((ch) << 1))

// レジスタアドレス (IOCON.BANK = 1 の配置)
#define MCP_IODIR_A 0x00  // 向き (1 = 入力、0 = 出力)
#define MCP_GPPU_A 0x06   // プルアップ (1 = 有効)
#define MCP_GPIO_A 0x09   // 読むとピンの状態、書くと出力ラッチ
#define MCP_OLAT_A 0x0A   // 出力ラッチ
#define MCP_IODIR_B 0x10
#define MCP_GPPU_B 0x16
#define MCP_GPIO_B 0x19
#define MCP_OLAT_B 0x1A
#define MCP_IOCON_BANK0 0x0A  // リセット直後 (BANK = 0) の IOCON のアドレス

// IOCON の設定値
#define IOCON_BANK 0x80  // レジスタをポート A / B ごとにまとめる (上の配置になる)
#define IOCON_HAEN 0x08  // ハードウェアアドレスを有効にする (同じ /CS の 2 個を区別する)
#define IOCON_ODR 0x04   // INT ピンをオープンドレインにする
#define MCP_IOCON_VALUE (IOCON_BANK | IOCON_HAEN | IOCON_ODR)  // 0x8C

#define MCP_ALL_INPUT 0xFF
#define MCP_ALL_OUTPUT 0x00

// =====================================================================
// ch7 GPB: カードの制御線とアドレスの上位 (ビット = 1 で High)。v3.0 (62256 なし) の割り当て
// =====================================================================
//   B0  カードの CE2 (High で選択)              カードの F5
//   B1  カードの /OE                            F7
//   B2  カードの /CE1                           F4
//   B3  カードの /WE                            F6
//   B4  A16、B5 A17、B6 A18、B7 A19             F32、F33、F34、F35 (0x00000-0x0FFFF では 0)
#define CTRL_CS2 0x01
#define CTRL_CARD_nOE 0x02
#define CTRL_CARD_nCE1 0x04
#define CTRL_nWE 0x08
#define CTRL_ADDR_HI 0xF0      // A16-A19
#define CTRL_ADDR_HI_SHIFT 12  // アドレスのビット 16-19 → B4-B7

// 状態ごとの値 (A16-A19 は 0。アドレスを出すときに足す)
//   待機       0x0F: /CE1 = H、CS2 = H、/OE = H、/WE = H (非選択)
//   カード選択 0x0B: /CE1 = L、CS2 = H
//   カード解放 0x0E: /CE1 = H、CS2 = L (1 バイトごとの後始末。CE2 も下げて二重に非選択にする)
#define CTRL_IDLE (CTRL_CS2 | CTRL_CARD_nOE | CTRL_CARD_nCE1 | CTRL_nWE)
#define CTRL_CARD_SELECT (CTRL_IDLE & ~CTRL_CARD_nCE1)
#define CTRL_CARD_RELEASE (CTRL_IDLE & ~CTRL_CS2)

// =====================================================================
// SPI SRAM 23LC512 (64 KB、/CS = D6)。本体だけの処理で使うのは 0x0000-0x7FFF
// =====================================================================
#define SRAM23_READ 0x03   // 読み出し: 03 アドレス上位 下位 → データ
#define SRAM23_WRITE 0x02  // 書き込み: 02 アドレス上位 下位 データ
#define SRAM23_RDMR 0x05   // モードレジスタ読み出し
#define SRAM23_WRMR 0x01   // モードレジスタ書き込み
#define SRAM23_MODE_MASK 0xC0
#define SRAM23_MODE_BYTE 0x00
#define SRAM23_MODE_PAGE 0x80
#define SRAM23_MODE_SEQUENTIAL 0x40  // 電源投入時の値。起動時にこれに揃える

#endif  // FSU_CONFIG_H
